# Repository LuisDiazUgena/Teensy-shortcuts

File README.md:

# Teensy-shortcuts

This programm is a shortcut manager for applications on your computer.
Up to 4 profiles (easy to implement more).
Up to 6 buttons with display info of each one. It's really simple to add more, but without showing info in the LCD Screen.

## Hardware

Use a Teensy 3.1 board, pushbuttons and a LCD to display the current Profile.

## Usage

The program is bassed on pushbuttons that send keyboard strokes on their rising edge.
Just click the button and let the magic happend!
## Software supported

1. Arduino IDE:
  1.  Verify
  2.  Upload
  3.  Monitor
  4.  Auto Format
2. Sublime Text 3 with Stino plugin :
  1.  Verify
  2.  Upload
  3.  Monitor
  4.  Auto Format

##How to: Add pushbuttons

1. Connect the pushbutton to a digital pin. Use a pulldown resistror to pushbuttons.
2. Create a Bounce objet to debounce the pushbutton:
<pre lang="arduino"><code>
  Bounce *name_of_your_button* = Bounce(*pin_of_your_button*,10);
</code></pre>
3. Use:
<pre lang="arduino"><code>
  pinMode(*pinNumer or variable*,INPUT);
</code></pre>
4. At <pre lang="Arduino">profileActions</pre> update the button, then watch for the risindEdge of that button and send keystrokes. ie:

<pre lang="arduino"><code>

  btn1.update();
   
  if (btn1.risingEdge()){
    Serial.println("risingEdge btn1");
    Keyboard.set_modifier(MODIFIERKEY_CTRL);
    Keyboard.set_key1(KEY_R);
    Keyboard.send_now();

  }
</code></pre>

##How to: Add program profile

Create a profile struct:
<pre lang="arduino"><code>    
  struct Profile profile1;
</code></pre>

Add profile name and shortcuts names:

<pre lang="arduino"><code>    
  strcpy (profile1.name,"Arduino IDE");
  strcpy (profile1.shortcut1,"Verify");
  strcpy (profile1.shortcut2,"Upload");
  strcpy (profile1.shortcut3,"Monitor");
  strcpy (profile1.shortcut4,"AutoFormat");
</code></pre>

Add shortcuts inside of <pre lang="arduino"><code>profileActions</code></pre> function

##How to: Add shortcuts

Check out your favorite program shortcuts and know which key combination activate them, then go to [teensy keys](https://www.pjrc.com/teensy/td_keyboard.html) and look for your keys combination.

Place them inside of:
<pre lang="arduino"><code>    
    if (name_of_your_button.risingEdge()){
      //Send keystrokes
    }
</code></pre>

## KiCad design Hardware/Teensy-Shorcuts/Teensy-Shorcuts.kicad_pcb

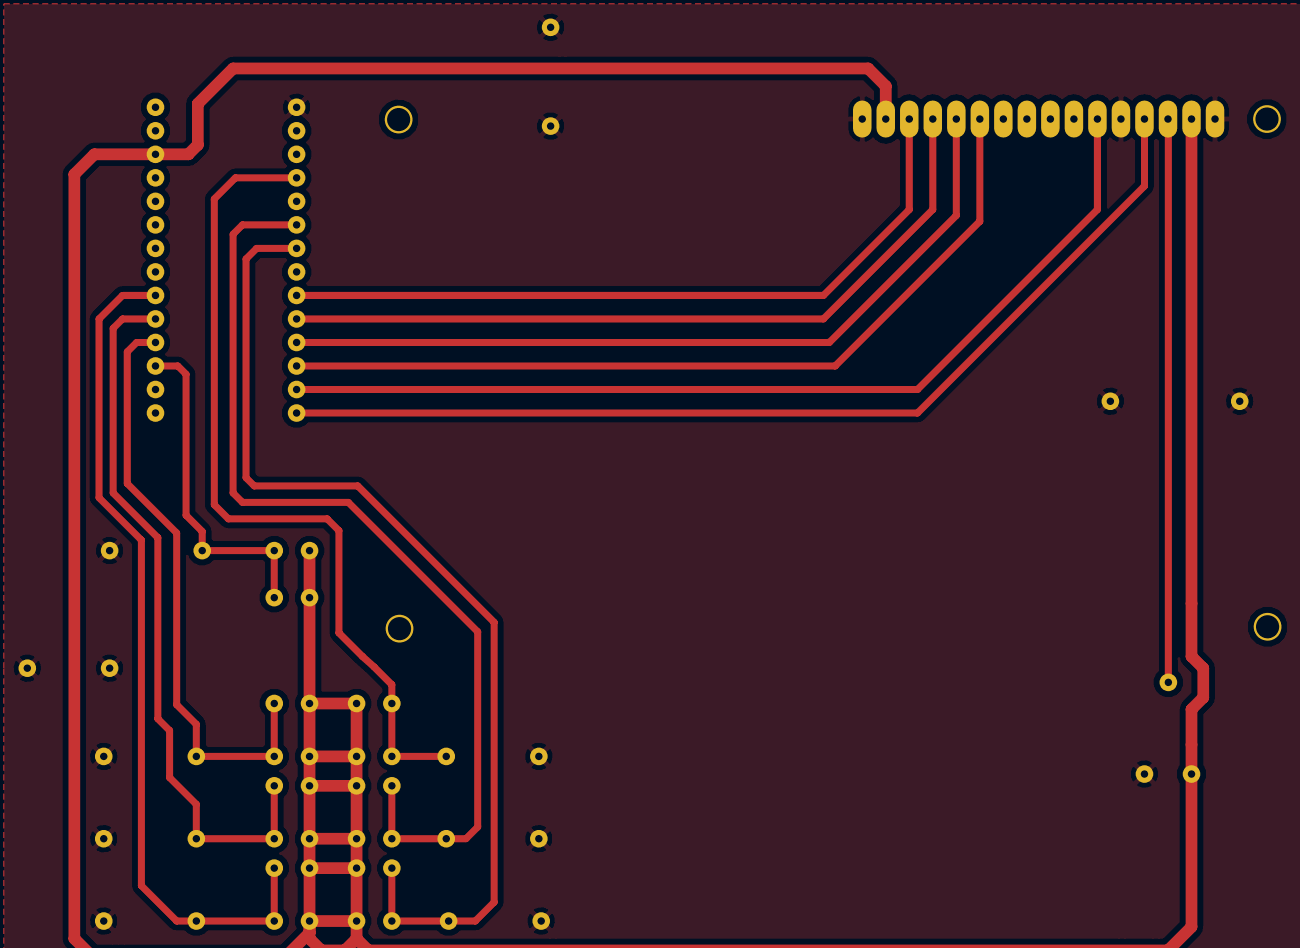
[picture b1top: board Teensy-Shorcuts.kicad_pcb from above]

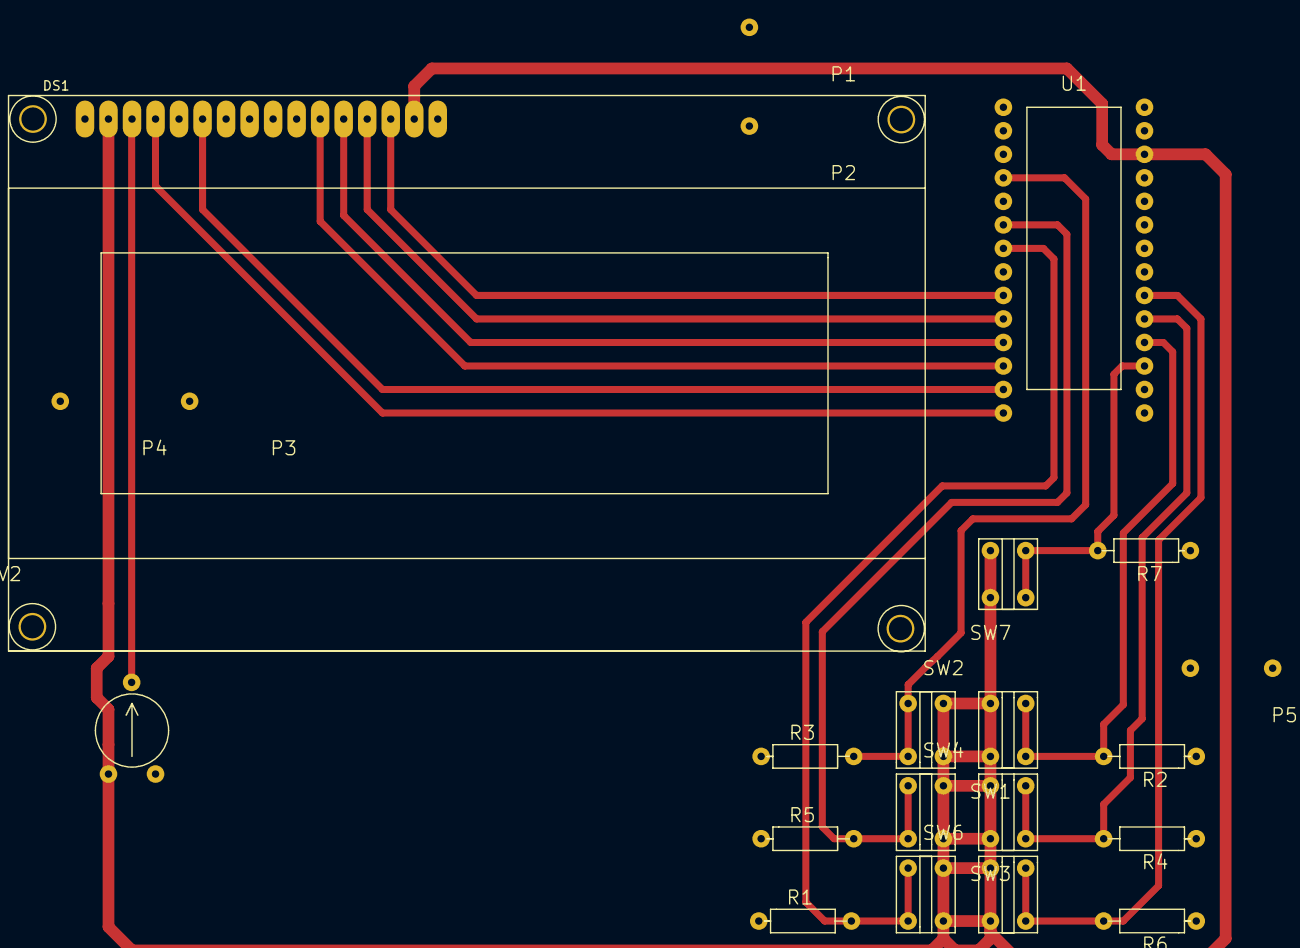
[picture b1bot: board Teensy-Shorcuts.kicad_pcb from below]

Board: 2 copper layers, 23 parts (23 on the bottom side), 16 nets.

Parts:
DS1: LCD20x4; LCD20X4
P1, P2, P3, P4, P5, P6: CONN_01X01; Jumper1x01
R1, R2, R3, R4, R5, R6, R7: 10KΩ; Res
RV2: 5KΩ; trimmer
SW1, SW2, SW3, SW4, SW5, SW6, SW7: SW_PUSH; Switch
U1: Teensy_3.1; Teensy-3.1

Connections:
7: DS1.14, U1.7
8: DS1.13, U1.8
9: DS1.12, U1.9
10: DS1.11, U1.10
11: DS1.6, U1.11
12: DS1.4, U1.12
GND: DS1.1, DS1.5, DS1.16, P1.1, P2.1, P3.1, P4.1, P5.1, P6.1, R1.1, R2.1, R3.1, R4.1, R5.1, R6.1, R7.1, RV2.3, U1.27
unnamed: DS1.3, RV2.2
PS: R7.2, SW7.2, U1.15
S0: R1.2, SW6.2, U1.5
S1: R2.2, SW1.2, U1.16
S2: R3.2, SW2.2, U1.2
S3: R4.2, SW3.2, U1.17
S4: R5.2, SW4.2, U1.4
S5: R6.2, SW5.2, U1.18
VCC: DS1.2, DS1.15, RV2.1, SW1.1, SW2.1, SW3.1, SW4.1, SW5.1, SW6.1, SW7.1, U1.24

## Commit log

2015-03-12 initial commit. Added suport for arduino ide
2015-03-12 modified README.me
2015-03-12 added how-to
2015-03-12 Added functions: selectProfile, printProfile, profileActions
2015-03-13 add profile struct
2015-03-13 Now is struct based. Added up to 4 profiles and 6 shorcuts by profile
2015-03-13 add profile2: Sublime text 3 with stino pluging
2015-03-13 Modified software supported and instructions
2015-03-13 added sublime text 3+stino support
2015-03-13 changed format
2015-03-14 Started to work on Hardware
2015-03-15 Added pushbuttons and lcd schematics
2015-03-15 modified pushbuttons pins. Modified from 4 to 6 pushbuttons available
2015-03-15 added profile selector trimmer
2015-03-15 modified lcd library
2015-03-16 added teensy 3.1/teensy 3.1 library created
2015-03-16 modified Teensy library
2015-03-16 added Teensy3.1 pinout
2015-03-16 Added profile control with pushbutton instead of trimmer
2015-03-16 Created Schematichs and PCB board layaot
2015-03-16 added info
2015-03-16 Deleted gerber test
2015-03-16 Fixed misspelled variable
2015-03-17 modified Pcb layout
2015-03-17 Modified pcb traces to delete 90º angles
2015-03-17 Modified autoformat profile 2 to match Astyle Formatter plugin by timonwong
2015-03-17 Minnor fixes
2015-03-18 Modified pushbuttons to fit real pushbuttons
2015-04-13 Added profile to html web editor
2015-04-13 Adjust switch module to fit better real part
2015-04-13 moved html editor shortcuts text to string variables
2015-04-13 Improved footprints to adjust better to real part
